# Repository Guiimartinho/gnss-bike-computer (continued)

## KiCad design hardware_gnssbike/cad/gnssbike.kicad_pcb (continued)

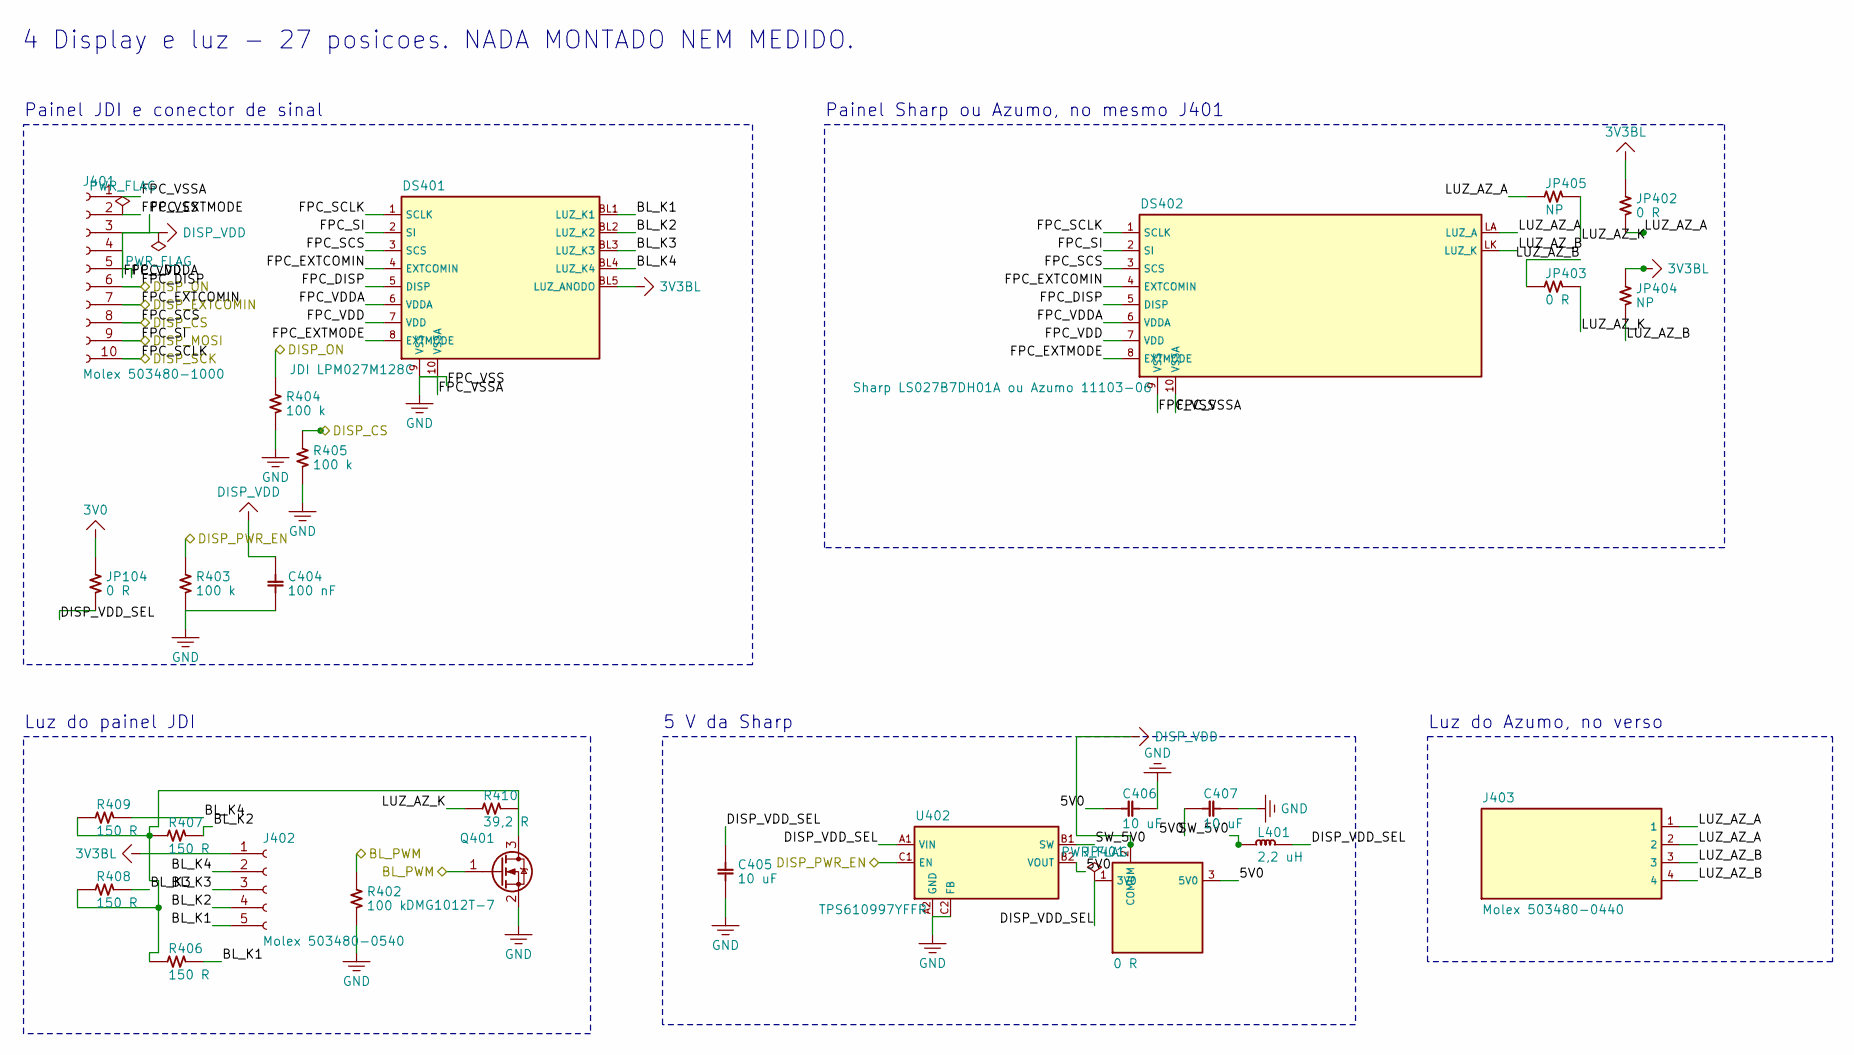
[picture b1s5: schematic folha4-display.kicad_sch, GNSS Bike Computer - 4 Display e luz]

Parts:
C404: 100 nF; C_0402_1005Metric
C405, C406, C407: 10 uF; C_0603_1608Metric
DS401: JDI LPM027M128C
DS402: Sharp LS027B7DH01A ou Azumo 11103-06
J401: Molex 503480-1000; Molex_503480-1000_1x10_P0.50mm
J402: Molex 503480-0540; Molex_503480-0540_1x05_P0.50mm
J403: Molex 503480-0440; Molex_503480-0440_1x04_P0.50mm
JP104, JP402, JP403: 0 R; R_0402_1005Metric
JP401: 0 R; JumperRF_3x0402
JP404, JP405: NP; R_0402_1005Metric
L401: 2,2 uH; L_Murata_DFE201610P
Q401: DMG1012T-7; SOT-523
R402, R403, R404, R405: 100 k; R_0402_1005Metric
R406, R407, R408, R409: 150 R; R_0402_1005Metric
R410: 39,2 R; R_0402_1005Metric
U402: TPS610997YFFR; Texas_DSBGA-6_0.855x1.255mm_Layout2x3_P0.4mm_LevelB

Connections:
3V0: JP104.1; also elsewhere on the board
3V3BL: DS401.BL5 (LUZ_ANODO), J402.1, JP402.1, JP404.1; also elsewhere on the board
5V0: C406.1, C407.1, JP401.3 (5V0), U402.B2 (VOUT)
BL_CATODO: Q401.3 (D), R406.2, R407.2, R408.2, R409.2, R410.2
BL_K1: DS401.BL1 (LUZ_K1), J402.5, R406.1
BL_K2: DS401.BL2 (LUZ_K2), J402.4, R407.1
BL_K3: DS401.BL3 (LUZ_K3), J402.3, R408.1
BL_K4: DS401.BL4 (LUZ_K4), J402.2, R409.1
BL_PWM: Q401.1 (G), R402.1; also elsewhere on the board
DISP_CS: DS401.3 (SCS), DS402.3 (SCS), J401.8, R405.1; also elsewhere on the board
DISP_ON: DS401.5 (DISP), DS402.5 (DISP), J401.6, R404.1; also elsewhere on the board
DISP_PWR_EN: R403.1, U402.C1 (EN); also elsewhere on the board
DISP_VDD: C404.1, DS401.6 (VDDA), DS401.7 (VDD), DS401.8 (EXTMODE), DS402.6 (VDDA), DS402.7 (VDD), DS402.8 (EXTMODE), J401.3, J401.4, J401.5, JP401.2 (COMUM)
DISP_VDD_SEL: C405.1, JP104.2, JP401.1 (3V0), L401.1, U402.A1 (VIN)
FPC_EXTCOMIN: DS401.4 (EXTCOMIN), DS402.4 (EXTCOMIN), J401.7; also elsewhere on the board
FPC_SCLK: DS401.1 (SCLK), DS402.1 (SCLK), J401.10; also elsewhere on the board
FPC_SI: DS401.2 (SI), DS402.2 (SI), J401.9; also elsewhere on the board
GND: C404.2, C405.2, C406.2, C407.2, DS401.9 (VSS), DS401.10 (VSSA), DS402.9 (VSS), DS402.10 (VSSA), J401.1, J401.2, Q401.2 (S), R402.2, R403.2, R404.2, R405.2, U402.A2 (GND), U402.C2 (FB); also elsewhere on the board
LUZ_AZ_A: DS402.LA (LUZ_A), J403.1, J403.2, JP402.2, JP405.1
LUZ_AZ_B: DS402.LK (LUZ_K), J403.3, J403.4, JP403.1, JP404.2
LUZ_AZ_K: JP403.2, JP405.2, R410.1
SW_5V0: L401.2, U402.B1 (SW)

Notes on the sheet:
Painel JDI e conector de sinal
Luz do painel JDI
5 V da Sharp
Painel Sharp ou Azumo, no mesmo J401
Luz do Azumo, no verso
4 Display e luz - 27 posicoes. NADA MONTADO NEM MEDIDO.

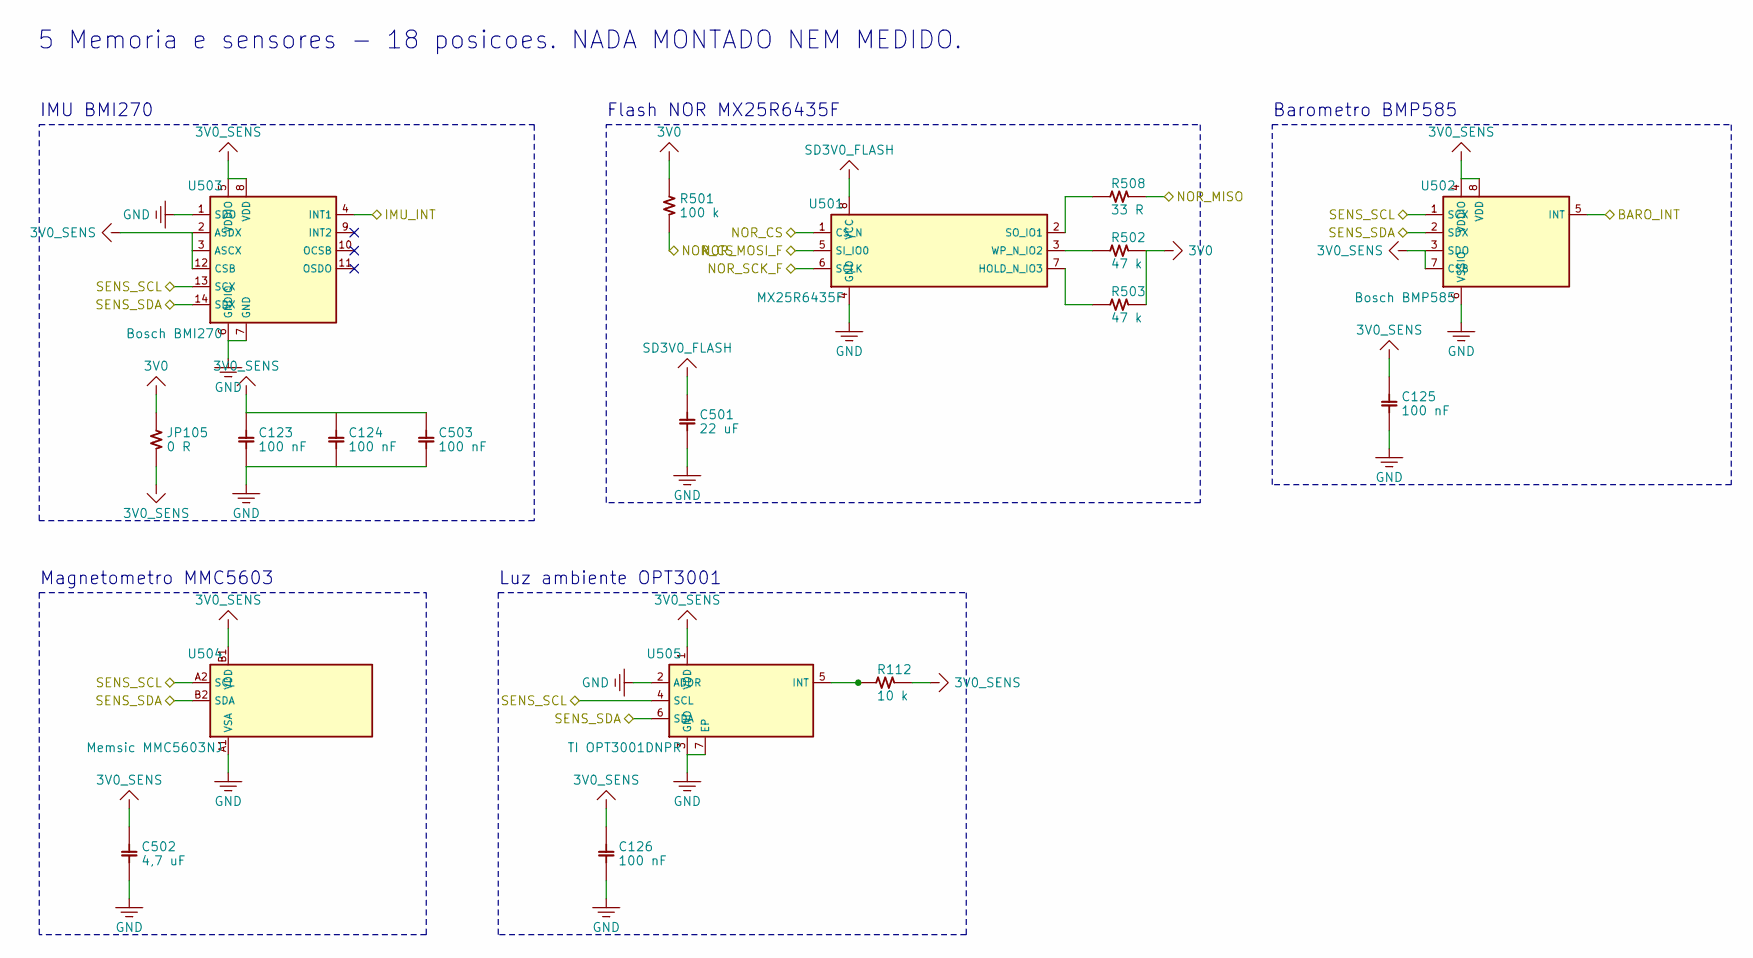
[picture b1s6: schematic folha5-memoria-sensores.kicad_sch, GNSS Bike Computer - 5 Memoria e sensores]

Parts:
C123, C124, C125, C126: 100 nF; C_0603_1608Metric
C501: 22 uF; C_0603_1608Metric
C502: 4,7 uF; C_0603_1608Metric
C503: 100 nF; C_0402_1005Metric
JP105: 0 R; R_0402_1005Metric
R112: 10 k; R_0402_1005Metric
R501: 100 k; R_0402_1005Metric
R502, R503: 47 k; R_0402_1005Metric
R508: 33 R; R_0402_1005Metric
U501: MX25R6435F; SOIC-8_5.275x5.275mm_P1.27mm
U502: Bosch BMP585; BMP585_LGA-8_3.25x3.25mm
U503: Bosch BMI270; Bosch_LGA-14_3x2.5mm_P0.5mm
U504: Memsic MMC5603NJ; MMC5603_WLP-4_0.82x0.82mm
U505: TI OPT3001DNPR; OPT3001_USON-6_2x2mm_P0.65mm

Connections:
3V0: JP105.1, R501.1, R502.1, R503.1; also elsewhere on the board
3V0_SENS: C123.1, C124.1, C125.1, C126.1, C502.1, C503.1, JP105.2, R112.1, U502.3 (SDO), U502.4 (VDDIO), U502.7 (CSB), U502.8 (VDD), U503.2 (ASDX), U503.3 (ASCX), U503.5 (VDDIO), U503.8 (VDD), U503.12 (CSB), U504.B1 (VDD), U505.1 (VDD); also elsewhere on the board
BARO_INT: U502.5 (INT); also elsewhere on the board
GND: C123.2, C124.2, C125.2, C126.2, C501.2, C502.2, C503.2, U501.4 (GND), U502.6 (VSSIO), U503.1 (SDO), U503.6 (GNDIO), U503.7 (GND), U504.A1 (VSA), U505.2 (ADDR), U505.3 (GND), U505.7 (EP); also elsewhere on the board
IMU_INT: U503.4 (INT1); also elsewhere on the board
INT_OPT: R112.2, U505.5 (INT)
NOR_CS: R501.2, U501.1 (CS_N); also elsewhere on the board
NOR_HOLD: R503.2, U501.7 (HOLD_N_IO3)
NOR_MISO: R508.1; also elsewhere on the board
NOR_MISO_F: R508.2, U501.2 (SO_IO1)
NOR_MOSI_F: U501.5 (SI_IO0); also elsewhere on the board
NOR_SCK_F: U501.6 (SCLK); also elsewhere on the board
NOR_WP: R502.2, U501.3 (WP_N_IO2)
SD3V0_FLASH: C501.1, U501.8 (VCC); also elsewhere on the board
SENS_SCL: U502.1 (SCX), U503.13 (SCX), U504.A2 (SCL), U505.4 (SCL); also elsewhere on the board
SENS_SDA: U502.2 (SDX), U503.14 (SDX), U504.B2 (SDA), U505.6 (SDA); also elsewhere on the board

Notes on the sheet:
Flash NOR MX25R6435F
IMU BMI270
Barometro BMP585
Magnetometro MMC5603
Luz ambiente OPT3001
5 Memoria e sensores - 18 posicoes. NADA MONTADO NEM MEDIDO.

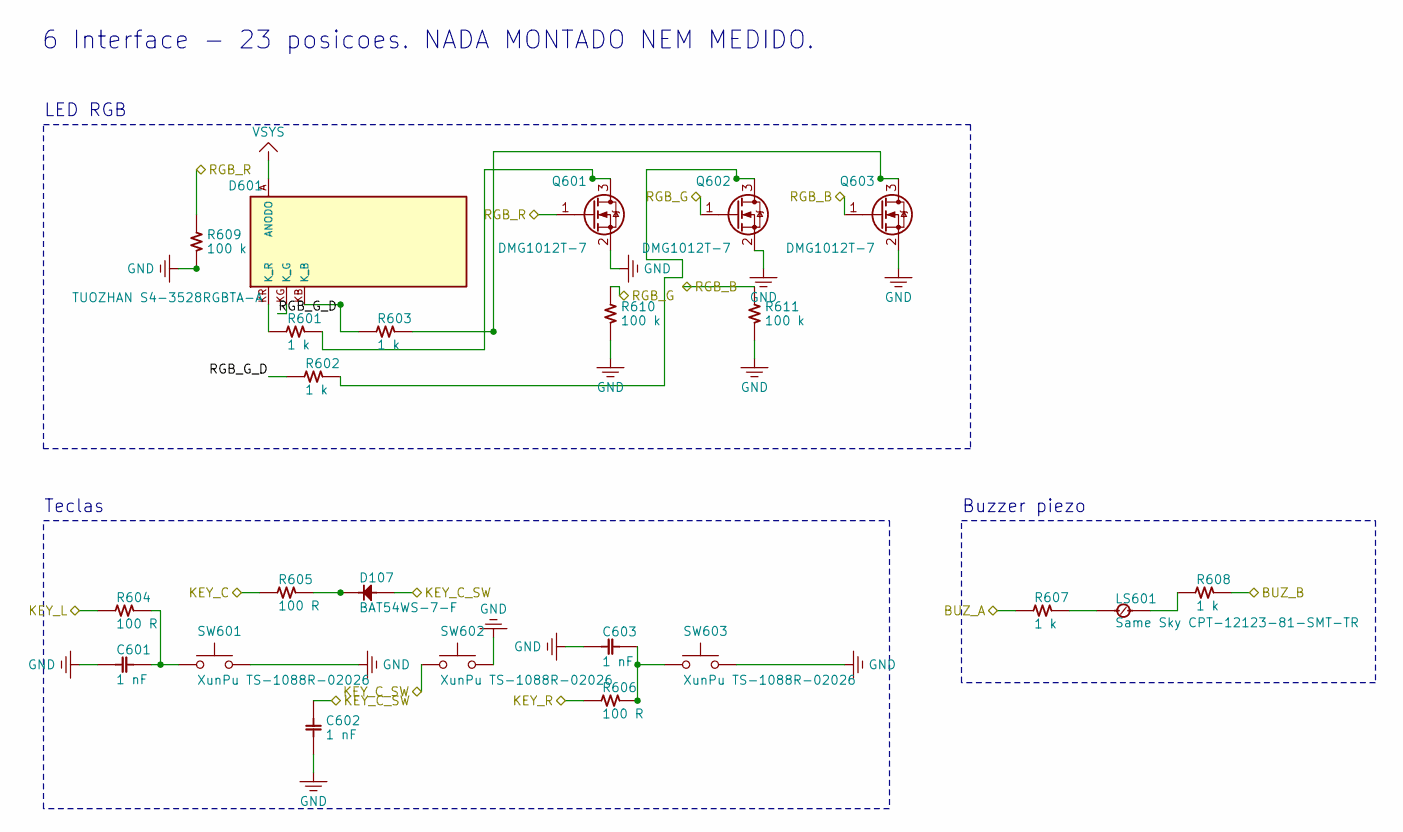
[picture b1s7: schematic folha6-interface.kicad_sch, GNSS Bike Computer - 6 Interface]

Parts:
C601, C602, C603: 1 nF; C_0603_1608Metric
D107: BAT54WS-7-F; D_SOD-323
D601: TUOZHAN S4-3528RGBTA-A; LED_RGB_3528_3.5x2.8mm
LS601: Same Sky CPT-12123-81-SMT-TR; Buzzer_CPT-12123-81-SMT_12x12mm
Q601, Q602, Q603: DMG1012T-7; SOT-523
R601, R602, R603, R607, R608: 1 k; R_0402_1005Metric
R604, R605, R606: 100 R; R_0402_1005Metric
R609, R610, R611: 100 k; R_0402_1005Metric
SW601, SW602, SW603: XunPu TS-1088R-02026; SW_TS-1088R_3.9x3mm

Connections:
BUZ_A: R607.1; also elsewhere on the board
BUZ_A_LS: LS601.1 (A), R607.2
BUZ_B: R608.1; also elsewhere on the board
BUZ_B_LS: LS601.2 (B), R608.2
GND: C601.2, C602.2, C603.2, Q601.2 (S), Q602.2 (S), Q603.2 (S), R609.2, R610.2, R611.2, SW601.2, SW602.2, SW603.2; also elsewhere on the board
KEY_C: R605.1; also elsewhere on the board
KEY_C_D: D107.2 (A), R605.2
KEY_C_SW: C602.1, D107.1 (K), SW602.1; also elsewhere on the board
KEY_L: R604.1; also elsewhere on the board
KEY_L_SW: C601.1, R604.2, SW601.1
KEY_R: R606.1; also elsewhere on the board
KEY_R_SW: C603.1, R606.2, SW603.1
RGB_B: Q603.1 (G), R611.1; also elsewhere on the board
RGB_B_D: D601.KB (K_B), R603.1
RGB_B_Q: Q603.3 (D), R603.2
RGB_G: Q602.1 (G), R610.1; also elsewhere on the board
RGB_G_D: D601.KG (K_G), R602.1
RGB_G_Q: Q602.3 (D), R602.2
RGB_R: Q601.1 (G), R609.1; also elsewhere on the board
RGB_R_D: D601.KR (K_R), R601.1
RGB_R_Q: Q601.3 (D), R601.2
VSYS: D601.A (ANODO); also elsewhere on the board

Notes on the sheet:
Teclas
LED RGB
Buzzer piezo
6 Interface - 23 posicoes. NADA MONTADO NEM MEDIDO.

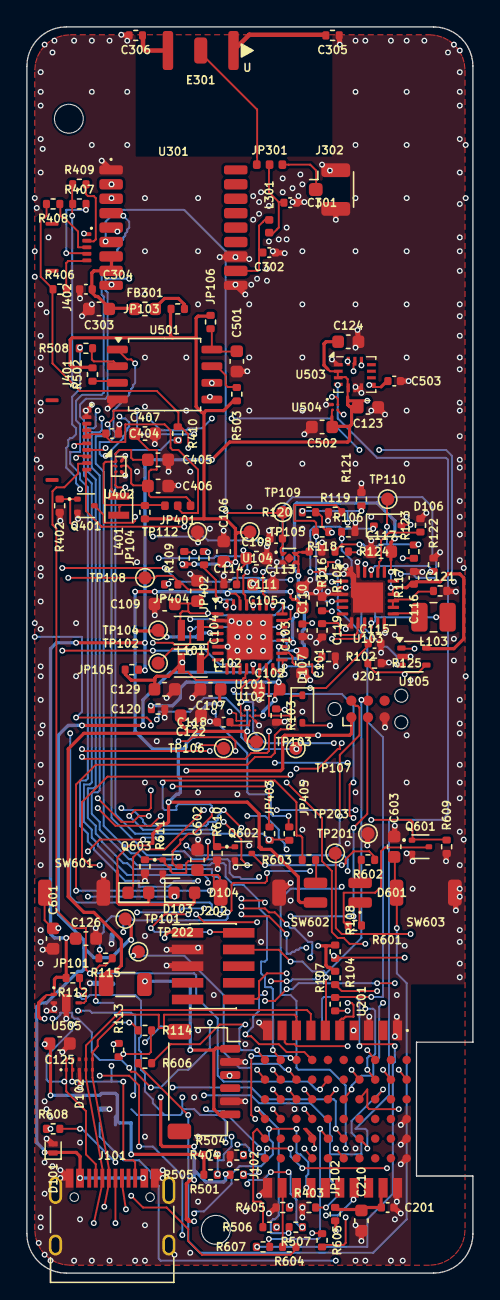
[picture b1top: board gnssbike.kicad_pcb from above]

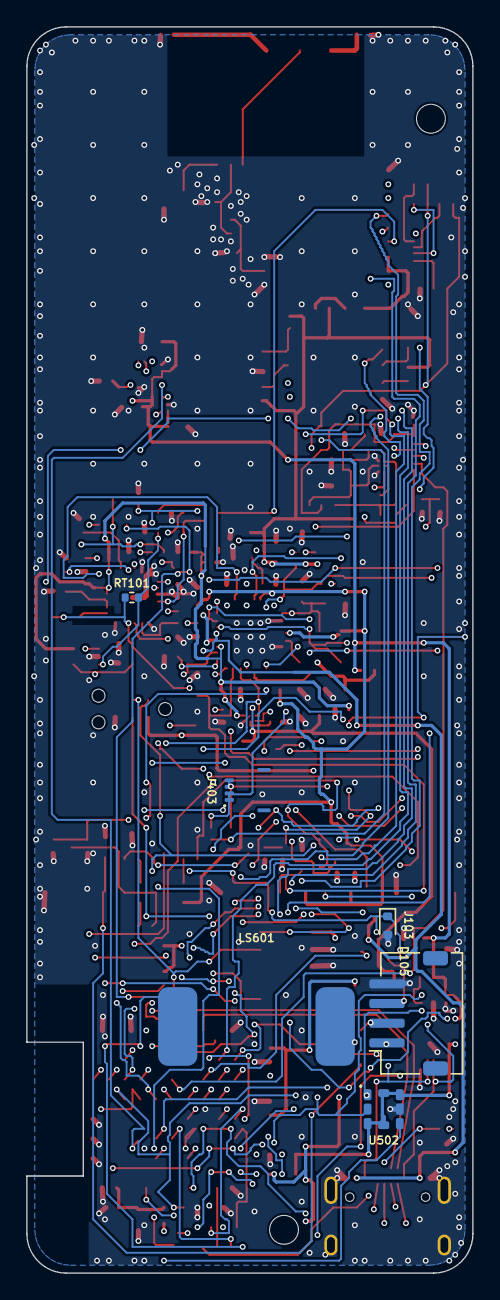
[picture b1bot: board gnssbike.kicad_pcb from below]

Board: 4 copper layers, 34.0 x 95.0 mm, 168 parts (6 on the bottom side), 118 nets.

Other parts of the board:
H1, H2: MountingHole_2.2mm_M2

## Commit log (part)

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2025-11-27 Initial commit for gnss-bike-computer
